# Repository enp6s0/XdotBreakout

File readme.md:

# xDot Breakout Board
A barebones breakout board for MultiTech xDot LoRa modules

## What does it do?
Breaks out xDot modules into stronger headers that doesn't break as easily, that's just about what it does. Geared towards prototyping needs but should be great for proof of concept prototypes also.

## License
CERN OHL-P v2, see license.md for more info

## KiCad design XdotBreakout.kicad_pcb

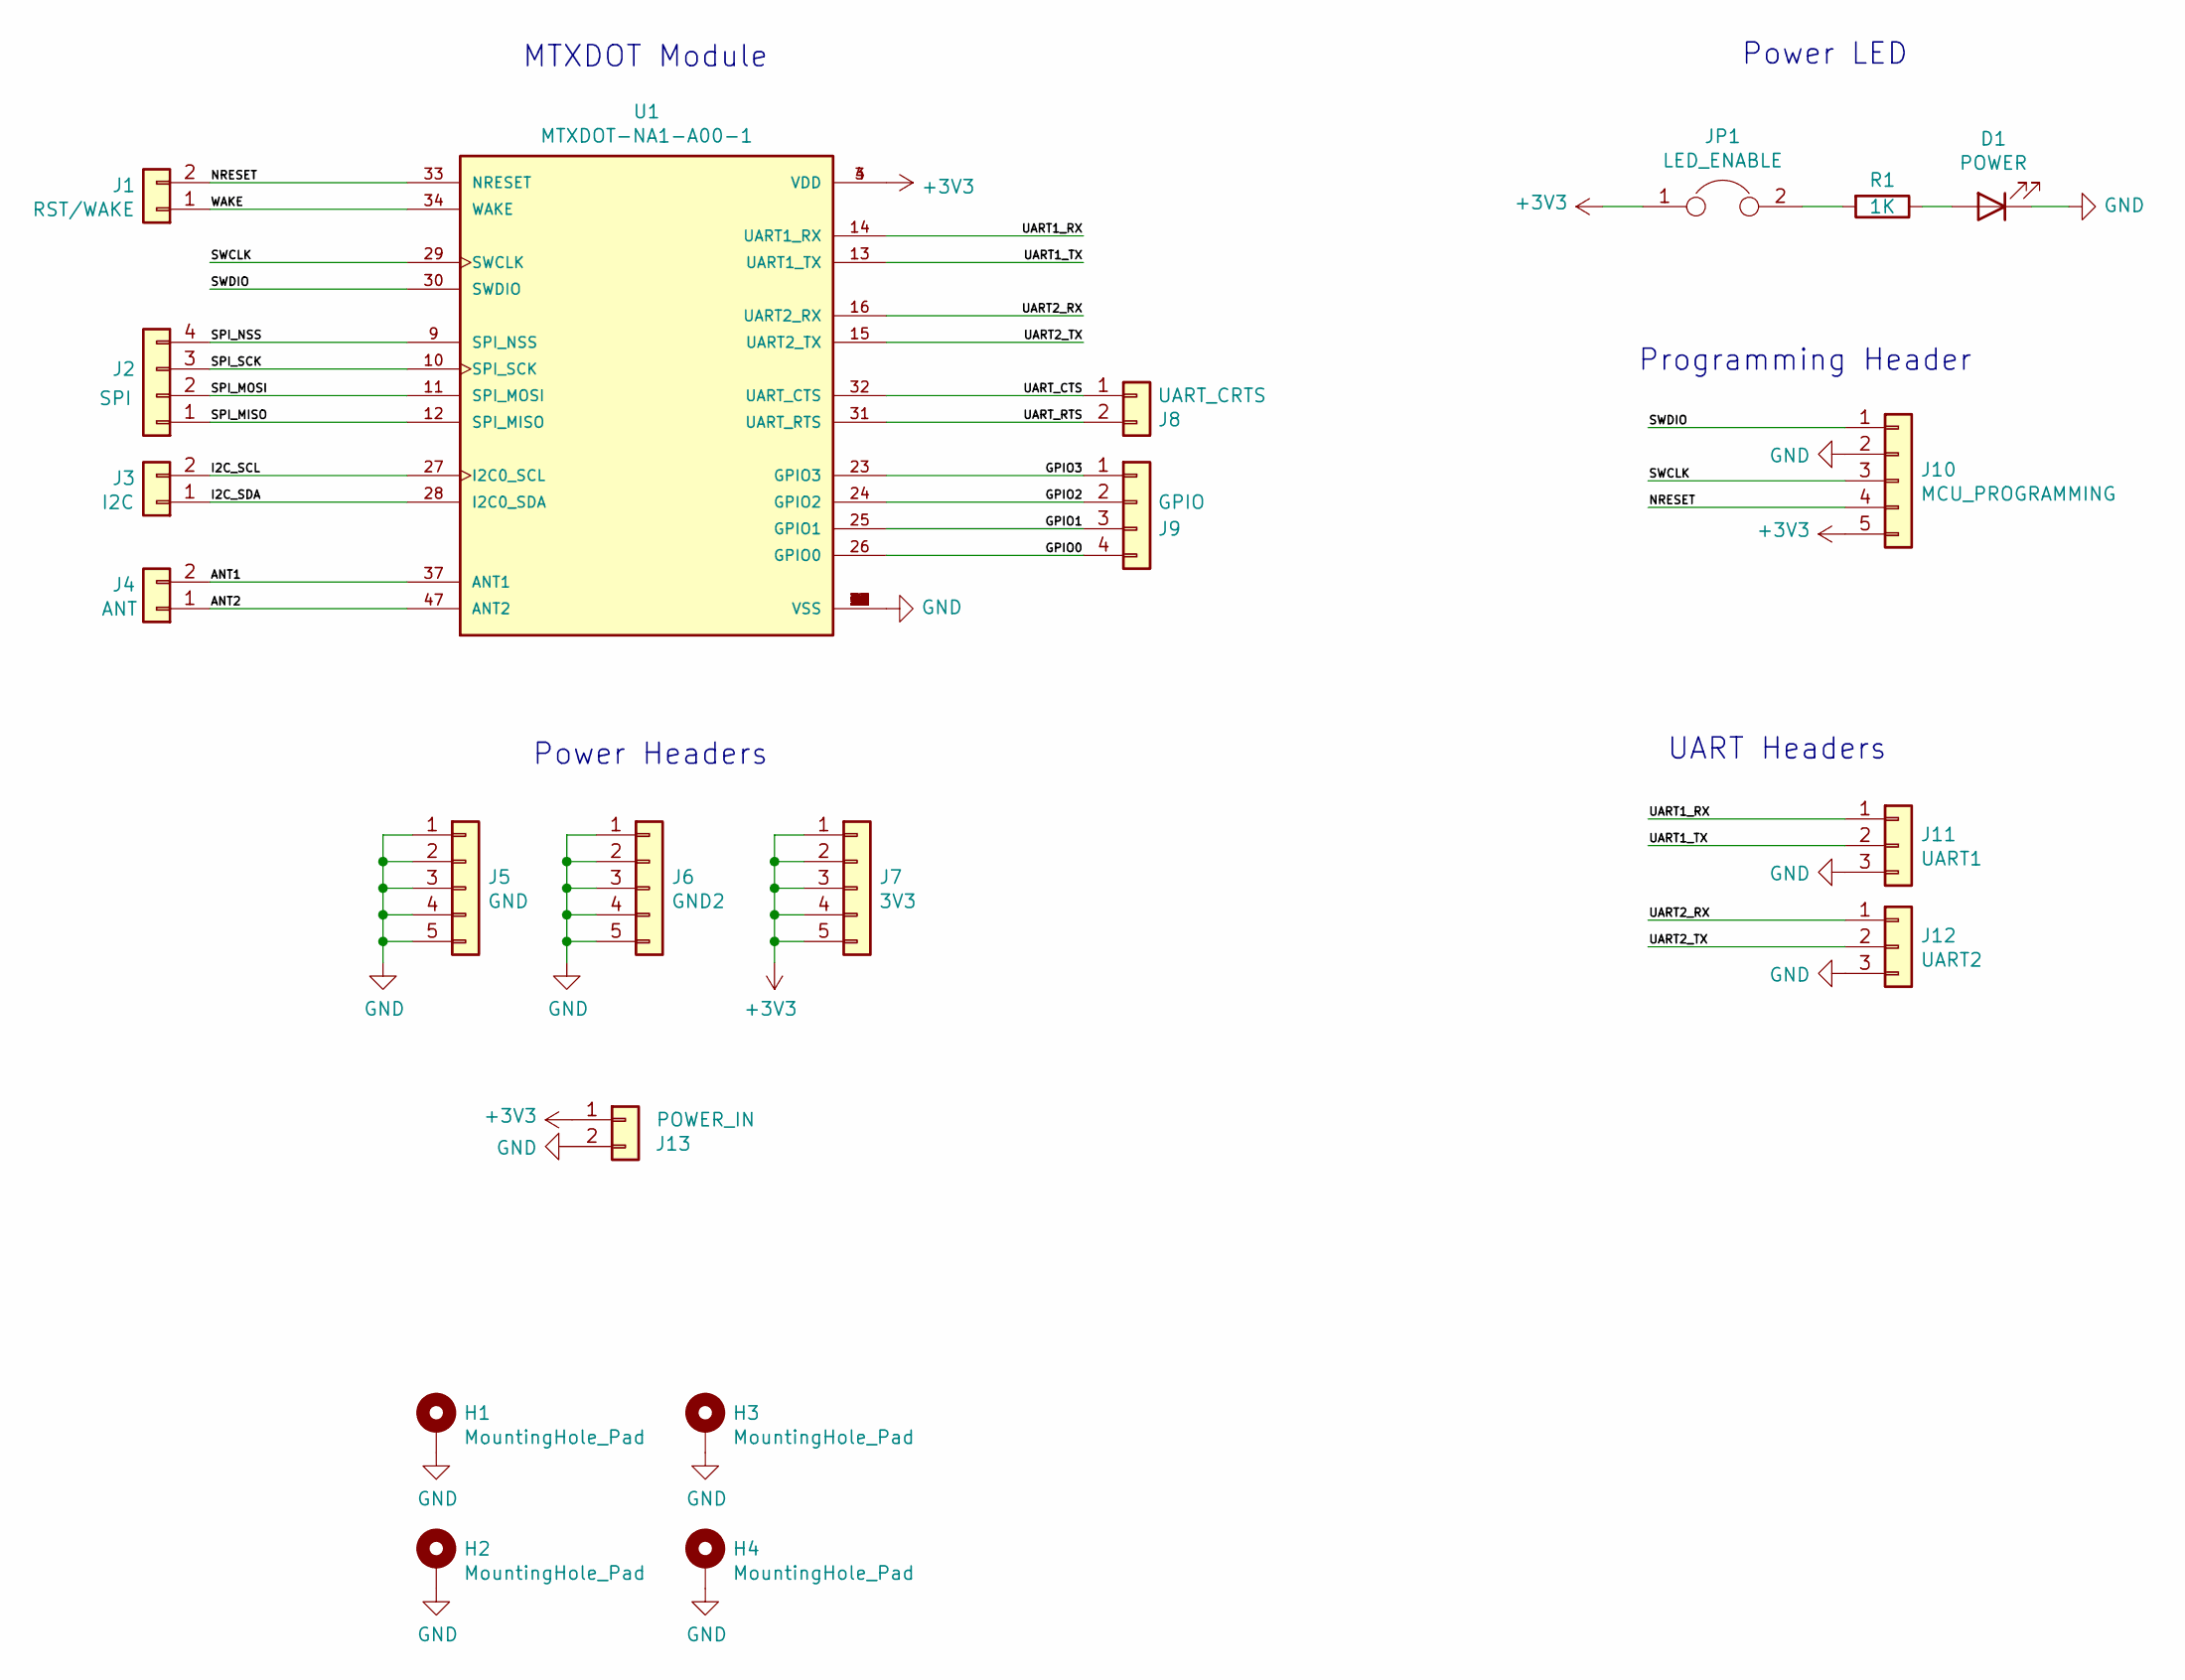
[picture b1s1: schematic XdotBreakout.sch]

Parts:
D1: POWER; LED_0603_1608Metric_Pad1.05x0.95mm_HandSolder
H1, H2, H3, H4: MountingHole_Pad; MountingHole_2.7mm_M2.5_Pad_Via
J1: RST/WAKE; PinHeader_1x02_P2.54mm_Vertical
J2: SPI; PinHeader_1x04_P2.54mm_Vertical
J3: I2C; PinHeader_1x02_P2.54mm_Vertical
J4: ANT; PinHeader_1x02_P2.54mm_Vertical
J5: GND; PinHeader_1x05_P2.54mm_Vertical
J6: GND2; PinHeader_1x05_P2.54mm_Vertical
J7: 3V3; PinHeader_1x05_P2.54mm_Vertical
J8: UART_CRTS; PinHeader_1x02_P2.54mm_Vertical
J9: GPIO; PinHeader_1x04_P2.54mm_Vertical
J10: MCU_PROGRAMMING; PinHeader_1x05_P2.54mm_Vertical
J11: UART1; PinHeader_1x03_P2.54mm_Vertical
J12: UART2; PinHeader_1x03_P2.54mm_Vertical
J13: POWER_IN; PinHeader_1x02_P2.54mm_Vertical
JP1: LED_ENABLE; PinHeader_1x02_P2.54mm_Vertical
R1: 1K; R_0603_1608Metric_Pad0.98x0.95mm_HandSolder
U1: MTXDOT-NA1-A00-1; XCVR_MTXDOT-NA1-A00-1

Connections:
+3V3: J7.1, J7.2, J7.3, J7.4, J7.5, J10.5, J13.1, JP1.1, U1.3 (VDD), U1.4 (VDD)
/ANT1: J4.2, U1.37 (ANT1)
/ANT2: J4.1, U1.47 (ANT2)
/GPIO0: J9.4, U1.26 (GPIO0)
/GPIO1: J9.3, U1.25 (GPIO1)
/GPIO2: J9.2, U1.24 (GPIO2)
/GPIO3: J9.1, U1.23 (GPIO3)
/I2C_SCL: J3.2, U1.27 (I2C0_SCL)
/I2C_SDA: J3.1, U1.28 (I2C0_SDA)
/NRESET: J1.2, J10.4, U1.33 (NRESET)
/SPI_MISO: J2.1, U1.12 (SPI_MISO)
/SPI_MOSI: J2.2, U1.11 (SPI_MOSI)
/SPI_NSS: J2.4, U1.9 (SPI_NSS)
/SPI_SCK: J2.3, U1.10 (SPI_SCK)
/SWCLK: J10.3, U1.29 (SWCLK)
/SWDIO: J10.1, U1.30 (SWDIO)
/UART1_RX: J11.1, U1.14 (UART1_RX)
/UART1_TX: J11.2, U1.13 (UART1_TX)
/UART2_RX: J12.1, U1.16 (UART2_RX)
/UART2_TX: J12.2, U1.15 (UART2_TX)
/UART_CTS: J8.1, U1.32 (UART_CTS)
/UART_RTS: J8.2, U1.31 (UART_RTS)
/WAKE: J1.1, U1.34 (WAKE)
GND: D1.1 (K), H1.1, H2.1, H3.1, H4.1, J5.1, J5.2, J5.3, J5.4, J5.5, J6.1, J6.2, J6.3, J6.4, J6.5, J10.2, J11.3, J12.3, J13.2, U1.1 (VSS), U1.5 (VSS), U1.17 (VSS), U1.20 (VSS), U1.35 (VSS), U1.36 (VSS), U1.38 (VSS), U1.39 (VSS), U1.40 (VSS), U1.41 (VSS), U1.42 (VSS), U1.43 (VSS), U1.44 (VSS), U1.45 (VSS), U1.46 (VSS), U1.48 (VSS), U1.49 (VSS), U1.50 (VSS), U1.51 (VSS), U1.52 (VSS), U1.53 (VSS), U1.54 (VSS), U1.55 (VSS), U1.56 (VSS), U1.57 (VSS), U1.58 (VSS)
unnamed: D1.2 (A), R1.1
unnamed: JP1.2, R1.2

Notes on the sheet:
MTXDOT Module
Power Headers
Power LED
Programming Header
UART Headers

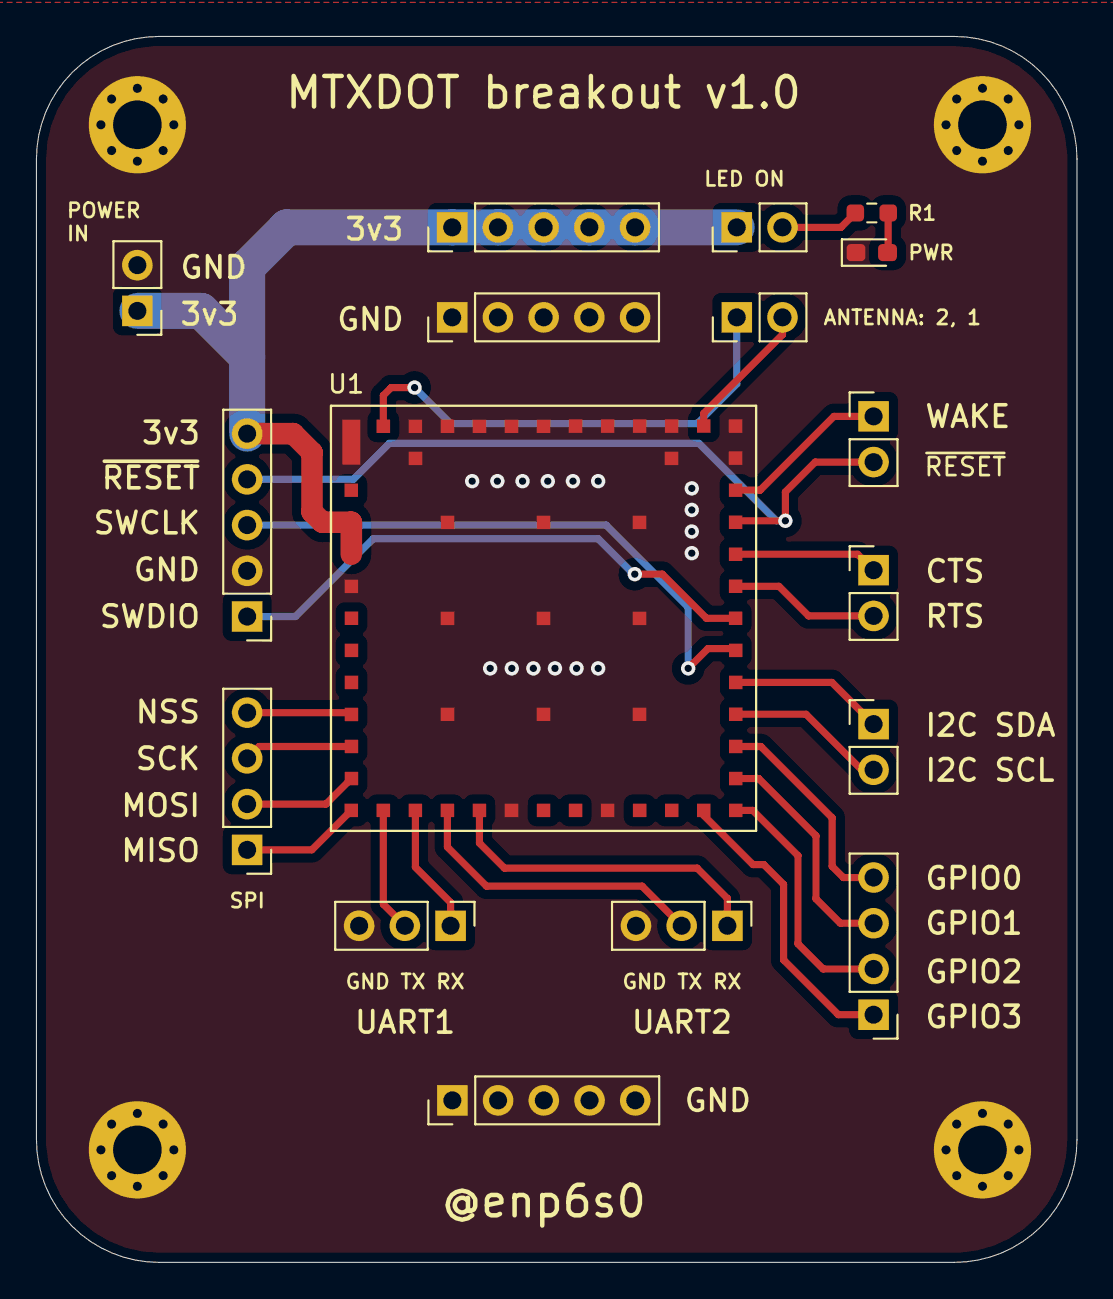
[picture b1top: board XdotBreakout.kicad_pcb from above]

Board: 2 copper layers, 57.8 x 68.1 mm, 21 parts (0 on the bottom side), 26 nets.

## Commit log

2021-10-05 First push
2021-10-05 Here comes the readme!
2021-10-05 Adding gitignore to ignore fab output
